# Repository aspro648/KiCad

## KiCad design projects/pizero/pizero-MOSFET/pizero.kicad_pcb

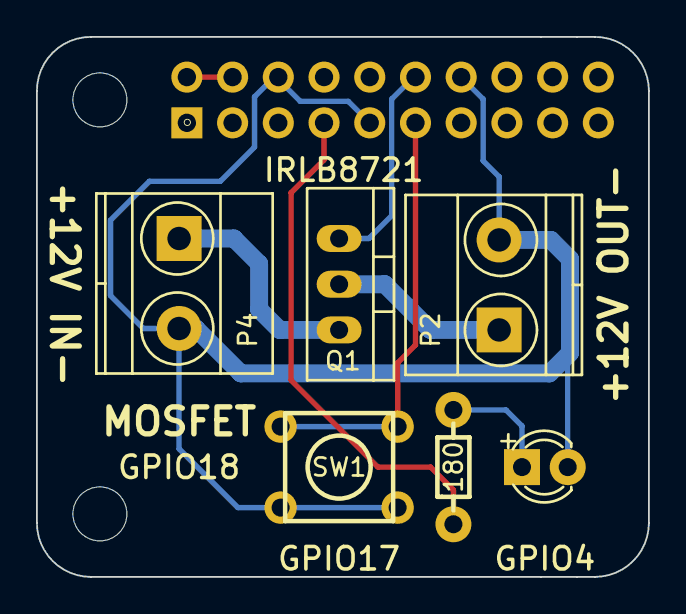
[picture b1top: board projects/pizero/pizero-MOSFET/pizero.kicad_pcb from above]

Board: 2 copper layers, 34.0 x 30.0 mm, 8 parts (0 on the bottom side), 8 nets.

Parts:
D1: LED; LED-3MM
P2, P4: CONN_01X02; TerminalBlock_Pheonix_MKDS1.5-2pol
P3: Raspberry_Pi_+_Conn; Pin_Header_Straight_2x10
Q1: Q_NMOS_GDS; TO-220_Neutral123_Vertical
R1: 180; Resistor_Horz
SW1: SPST; SW_PUSH_SMALL
VAL: MadeInOregonRev25

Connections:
GND: D1.1, P2.2, P3.6, P3.9, P3.14, P4.2, SW1.2
unnamed: D1.2, R1.1
unnamed: P2.1, Q1.2
unnamed: P3.7, R1.2
unnamed: P3.11, SW1.1
unnamed: P3.12, Q1.1
unnamed: P4.1, Q1.3
VCC: P3.2, P3.4

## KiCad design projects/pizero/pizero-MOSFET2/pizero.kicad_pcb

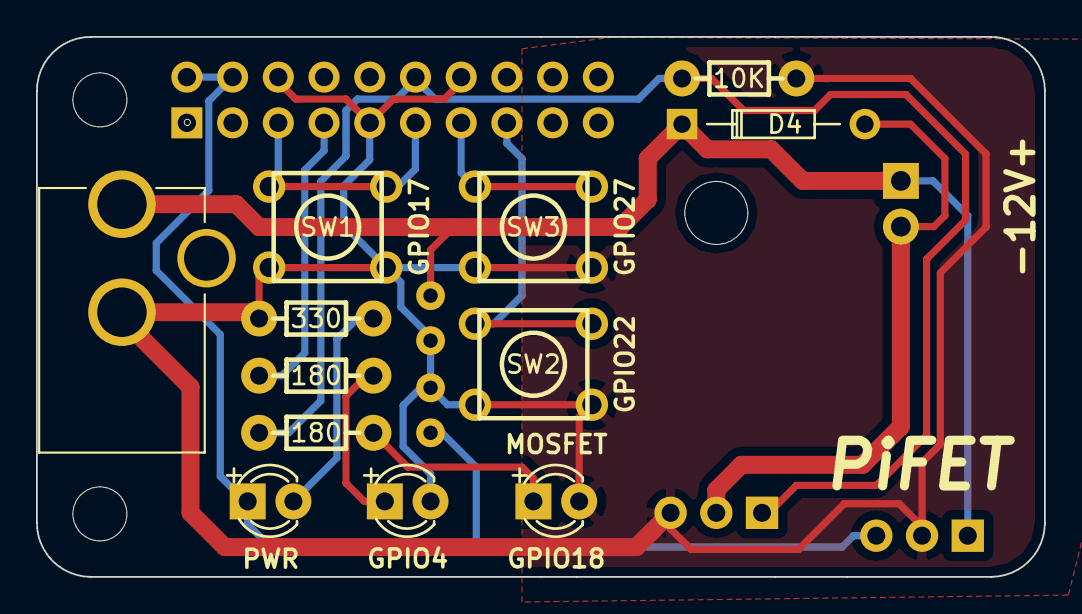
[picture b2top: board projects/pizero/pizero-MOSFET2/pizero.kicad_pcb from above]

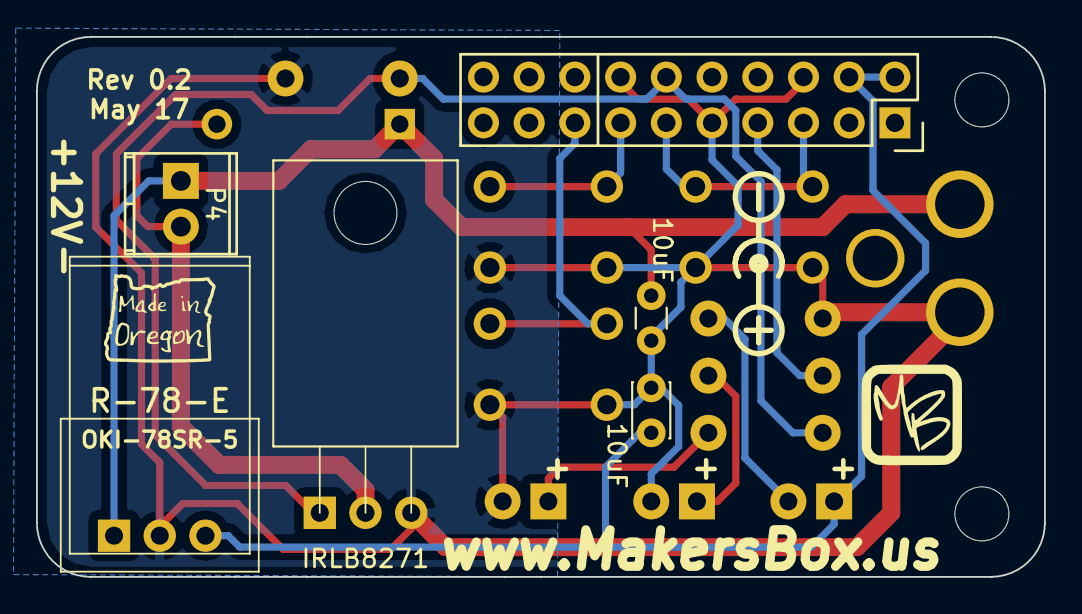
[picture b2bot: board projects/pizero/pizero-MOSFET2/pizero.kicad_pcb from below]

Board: 2 copper layers, 56.0 x 30.0 mm, 20 parts (5 on the bottom side), 12 nets.

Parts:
C1: 10uF; C_Disc_D3.0mm_W1.6mm_P2.50mm
C2: 10uF; C_Disc_D3.0mm_W2.0mm_P2.50mm
D1, D2, D3: LED; LED-3MM
D4: D; Diode_DO-35_SOD27_Horizontal_RM10
J1: BARREL_JACK
P3: Raspberry_Pi_+_Conn; Pin_Header_Straight_2x10
P4: CONN_01X02; TerminalBlock_Pheonix_MPT-2.54mm_2pol
Q1: IRLB8271; TO-220_Horizontal
R1, R4: 180; Resistor_Horz
R2: 10K; Resistor_Horz
R3: 330; Resistor_Horz
SW1, SW2, SW3: SPST; SW_PUSH_SMALL
U1: R-78-E
VAL: MadeInOregonRev25
VAL#2: MB225rev

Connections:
+5V: C2.1, D2.2, P3.2, P3.4, U1.3
+12V: C1.1, D4.1, J1.1, P4.1, U1.1
GND: C1.2, C2.2, D1.1, D3.1, J1.2, P3.6, P3.9, P3.14, Q1.3, R2.2, R3.2, SW1.2, SW2.2, SW3.2, U1.2
unnamed: D1.2, R1.1
unnamed: D2.1, R3.1
unnamed: D3.2, R4.1
unnamed: D4.2, P4.2, Q1.2
unnamed: P3.7, R1.2
unnamed: P3.5, P3.11, SW1.1
unnamed: P3.12, Q1.1, R2.1, R4.2
unnamed: P3.13, SW3.1
unnamed: P3.15, SW2.1

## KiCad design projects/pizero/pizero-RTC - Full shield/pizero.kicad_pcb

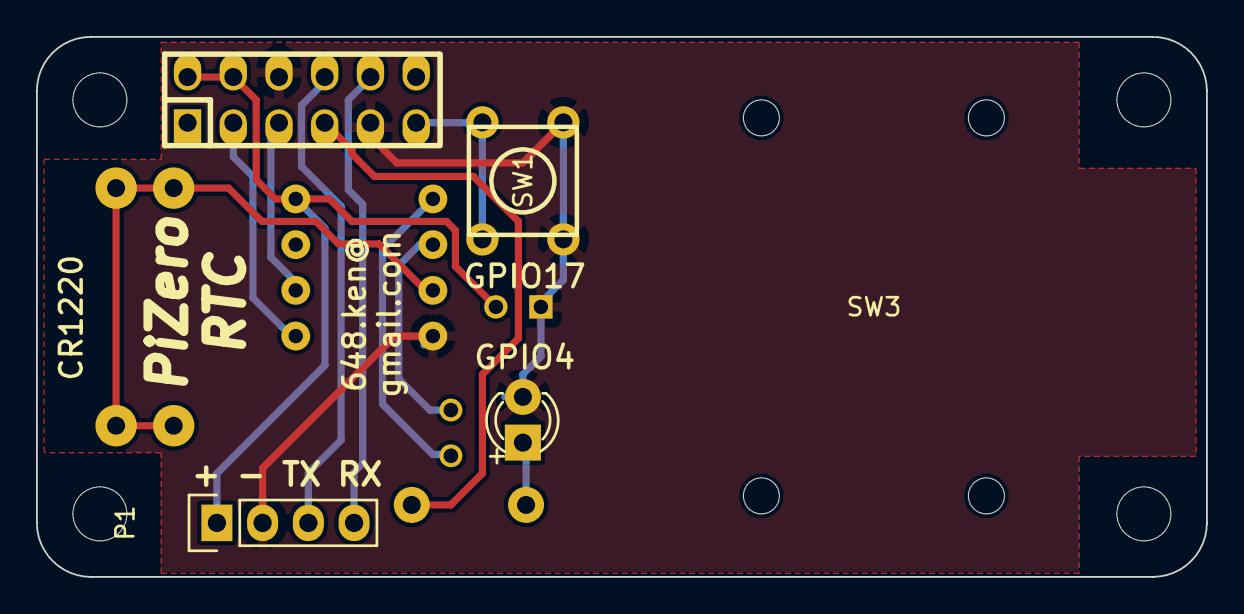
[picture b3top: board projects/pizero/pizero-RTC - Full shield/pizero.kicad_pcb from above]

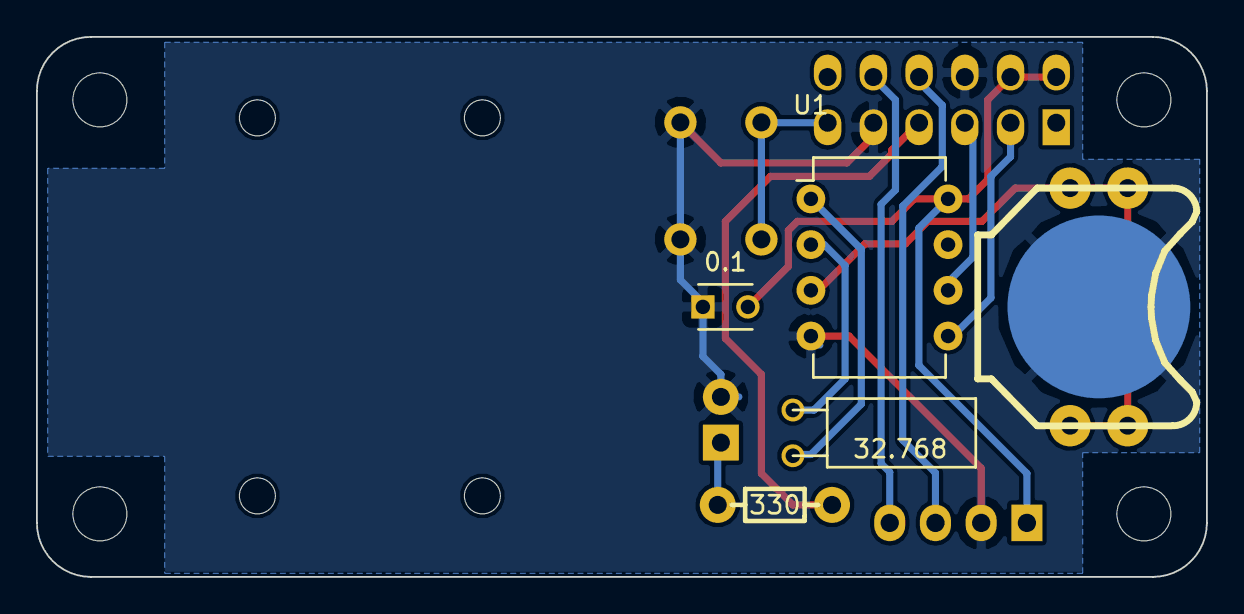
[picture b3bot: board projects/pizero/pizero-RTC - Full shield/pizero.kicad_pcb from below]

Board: 2 copper layers, 65.0 x 30.0 mm, 10 parts (5 on the bottom side), 12 nets.

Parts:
0.1: C_Small; C_Disc_D3_P2.5
32.768: Crystal; Crystal_Watch
BT1: Battery; BATT_12mm_TH
D1: LED; LED-3MM
P1: CONN_01X04; Pin_Header_Straight_1x04
P3: Raspberry_Pi_+_Conn; pin_socket_20x2
R1: 330; Resistor_Horz
SW1: SPST; SW_PUSH_SMALL
SW3: SW_PUSHBUTTON; SW_PUSH_SMALL
U1: DS1307+; DIP-8_W7.62mm

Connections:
GND: 0.1.1, BT1.2, D1.1, P1.2, P3.6, P3.9, SW1.2, U1.4
unnamed: 32.768.1, U1.1
unnamed: 32.768.2, U1.2
unnamed: BT1.1, U1.3
unnamed: D1.2, R1.1
unnamed: P1.3, P3.8
unnamed: P1.4, P3.10
unnamed: P3.3, U1.5
unnamed: P3.5, U1.6
unnamed: P3.7, R1.2
unnamed: P3.11, SW1.1
VCC: 0.1.2, P1.1, P3.2, P3.4, U1.8

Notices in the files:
projects/pizero/pizero-MOSFET/pizero.kicad_pcb:
License: CERN OHL V1.2
